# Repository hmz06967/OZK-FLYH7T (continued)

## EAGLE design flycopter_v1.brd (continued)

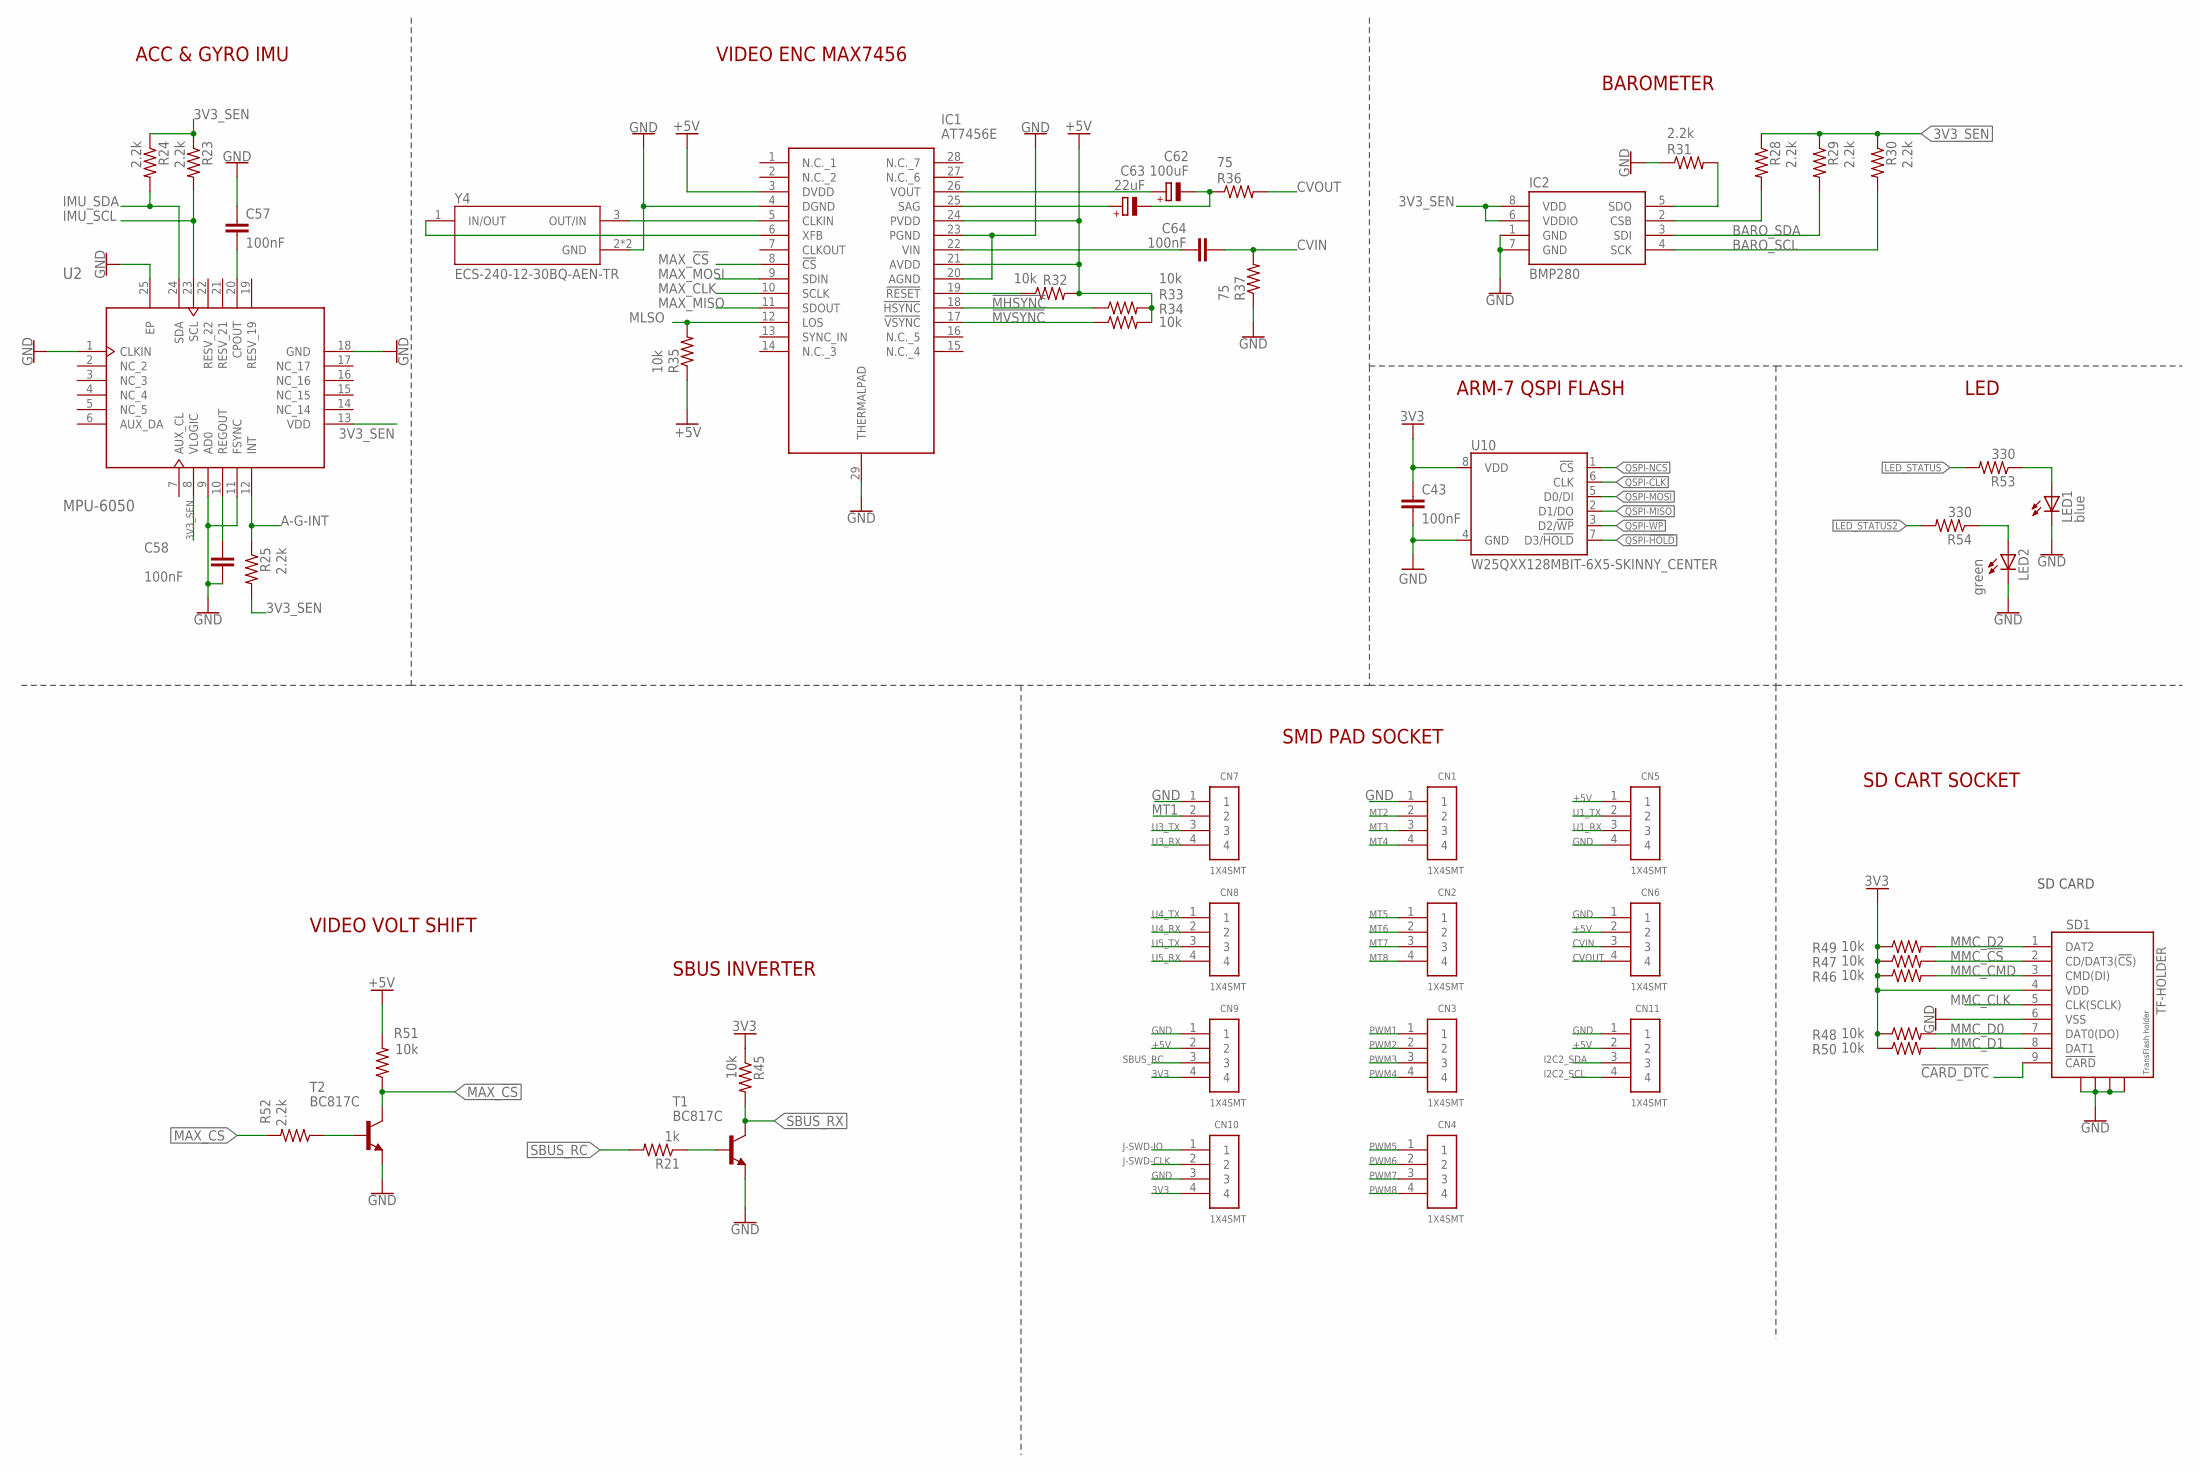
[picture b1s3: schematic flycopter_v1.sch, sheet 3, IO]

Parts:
C43, C57, C58, C64: 100nF; C0603K
C62: 100uF; A/3216-18R
C63: 22uF; A/3216-18R
CN1, CN2, CN3, CN4, CN5, CN6, CN7, CN8, CN9, CN10, CN11: 1X4SMT; 1X4-SMT
IC1: AT7456E; SOP65P640X120-29N
IC2: BMP280
LED1: blue; CHIPLED_0603
LED2: green; CHIPLED_0603
R21: 1k; R0402
R23, R24, R25, R28, R29, R30, R31, R52: 2.2k; R0402
R32, R33, R34, R35, R45, R46, R47, R48, R49, R50, R51: 10k; R0402
R36, R37: 75; R0402
R53, R54: 330; R0402
SD1: TF-HOLDER; TF-PULL
T1, T2: BC817C; SOT23-BEC
U2: MPU-6050; 24-VFQFN
U10: W25QXX128MBIT-6X5-SKINNY_CENTER; WSON-8-6X5-SKINNY_CENTERPAD
Y4: ECS-240-12-30BQ-AEN-TR; XTAL_ECS-240-12-30BQ-AEN-TR

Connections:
3V3: C43.1, CN9.4, CN10.4, R45.1, R46.1, R47.1, R48.1, R49.1, R50.1, SD1.4 (VDD), U10.8 (VDD); also elsewhere on the board
3V3_SEN: IC2.6 (VDDIO), IC2.8 (VDD), R23.1, R24.1, R25.2, R28.1, R29.1, R30.1, U2.8 (VLOGIC), U2.13 (VDD); also elsewhere on the board
!CARD_DTC: SD1.9 (!CARD); also elsewhere on the board
!MHSYNC: IC1.18 (!HSYNC), R33.1
!MVSYNC: IC1.17 (!VSYNC), R34.1
+5V: CN5.1, CN6.2, CN9.2, CN11.2, IC1.3 (DVDD), IC1.21 (AVDD), IC1.24 (PVDD), R32.2, R33.2, R34.2, R35.1, R51.2; also elsewhere on the board
A-G-INT: R25.1, U2.12 (INT)
BARO_SCL: IC2.4 (SCK), R30.2; also elsewhere on the board
BARO_SDA: IC2.3 (SDI), R29.2; also elsewhere on the board
CVIN: C64.2, CN6.3, R37.2
CVOUT: CN6.4, R36.2
GND: C43.2, C57.1, C58.2, CN1.1, CN5.4, CN6.1, CN7.1, CN9.1, CN10.3, CN11.1, IC1.4 (DGND), IC1.20 (AGND), IC1.23 (PGND), IC1.29 (THERMALPAD), IC2.1 (GND), IC2.7 (GND), LED1.C, LED2.C, R31.1, R37.1, SD1.6 (VSS), SD1.S1, SD1.S2, SD1.S3, SD1.S4, T1.E, T2.E, U2.1 (CLKIN), U2.9 (AD0), U2.11 (FSYNC), U2.18 (GND), U2.25 (EP), U10.4 (GND), Y4.2 (GND), Y4.4 (GND); also elsewhere on the board
I2C2_SCL: CN11.4; also elsewhere on the board
I2C2_SDA: CN11.3; also elsewhere on the board
IMU_SCL: R23.2, U2.23 (SCL); also elsewhere on the board
IMU_SDA: R24.2, U2.24 (SDA); also elsewhere on the board
J-SWD-CLK: CN10.2; also elsewhere on the board
J-SWD-IO: CN10.1; also elsewhere on the board
LED_STATUS: R53.2; also elsewhere on the board
LED_STATUS2: R54.2; also elsewhere on the board
MAX_!CS: IC1.8 (!CS), R51.1, T2.C
MAX_CLK: IC1.10 (SCLK); also elsewhere on the board
MAX_CS: R52.2; also elsewhere on the board
MAX_MISO: IC1.11 (SDOUT); also elsewhere on the board
MAX_MOSI: IC1.9 (SDIN); also elsewhere on the board
MLSO: IC1.12 (LOS), R35.2
MMC_!CS: R47.2, SD1.2 (CD/DAT3(!CS!)); also elsewhere on the board
MMC_CLK: SD1.5 (CLK(SCLK)); also elsewhere on the board
MMC_CMD: R46.2, SD1.3 (CMD(DI)); also elsewhere on the board
MMC_D0: R48.2, SD1.7 (DAT0(DO)); also elsewhere on the board
MMC_D1: R50.2, SD1.8 (DAT1); also elsewhere on the board
MMC_D2: R49.2, SD1.1 (DAT2); also elsewhere on the board
MT1: CN7.2; also elsewhere on the board
MT2: CN1.2; also elsewhere on the board
MT3: CN1.3; also elsewhere on the board
MT4: CN1.4; also elsewhere on the board
MT5: CN2.1; also elsewhere on the board
MT6: CN2.2; also elsewhere on the board
MT7: CN2.3; also elsewhere on the board
MT8: CN2.4; also elsewhere on the board
unnamed: R21.1, T1.B
unnamed: LED1.A, R53.1
unnamed: LED2.A, R54.1
unnamed: R52.1, T2.B
unnamed: IC1.19 (!RESET), R32.1
unnamed: C57.2, U2.20 (CPOUT)
unnamed: C58.1, U2.10 (REGOUT)
unnamed: C62.+, IC1.26 (VOUT)
unnamed: IC2.2 (CSB), R28.2
unnamed: IC2.5 (SDO), R31.2
unnamed: C63.+, IC1.25 (SAG)
unnamed: C62.-, C63.-, R36.1
unnamed: C64.1, IC1.22 (VIN)
unnamed: IC1.6 (XFB), Y4.1 (IN/OUT)
unnamed: IC1.5 (CLKIN), Y4.3 (OUT/IN)
PWM1: CN3.1; also elsewhere on the board
PWM2: CN3.2; also elsewhere on the board
PWM3: CN3.3; also elsewhere on the board
PWM4: CN3.4; also elsewhere on the board
PWM5: CN4.1; also elsewhere on the board
PWM6: CN4.2; also elsewhere on the board
PWM7: CN4.3; also elsewhere on the board
PWM8: CN4.4; also elsewhere on the board
QSPI-!HOLD: U10.7 (D3/!HOLD!); also elsewhere on the board
QSPI-!WP: U10.3 (D2/!WP!); also elsewhere on the board
QSPI-CLK: U10.6 (CLK); also elsewhere on the board
QSPI-MISO: U10.2 (D1/DO); also elsewhere on the board
QSPI-MOSI: U10.5 (D0/DI); also elsewhere on the board
QSPI-NCS: U10.1 (!CS!); also elsewhere on the board
SBUS_RC: CN9.3, R21.2
SBUS_RX: R45.2, T1.C; also elsewhere on the board
U1_RX: CN5.3; also elsewhere on the board
U1_TX: CN5.2; also elsewhere on the board
U3_RX: CN7.4; also elsewhere on the board
U3_TX: CN7.3; also elsewhere on the board
U4_RX: CN8.2; also elsewhere on the board
U4_TX: CN8.1; also elsewhere on the board
U5_RX: CN8.4; also elsewhere on the board
U5_TX: CN8.3; also elsewhere on the board

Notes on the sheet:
ACC & GYRO IMU
VIDEO ENC MAX7456
BAROMETER
SD CARD
SBUS INVERTER
SD CART SOCKET
ARM-7 QSPI FLASH
LED
VIDEO VOLT SHIFT
SMD PAD SOCKET

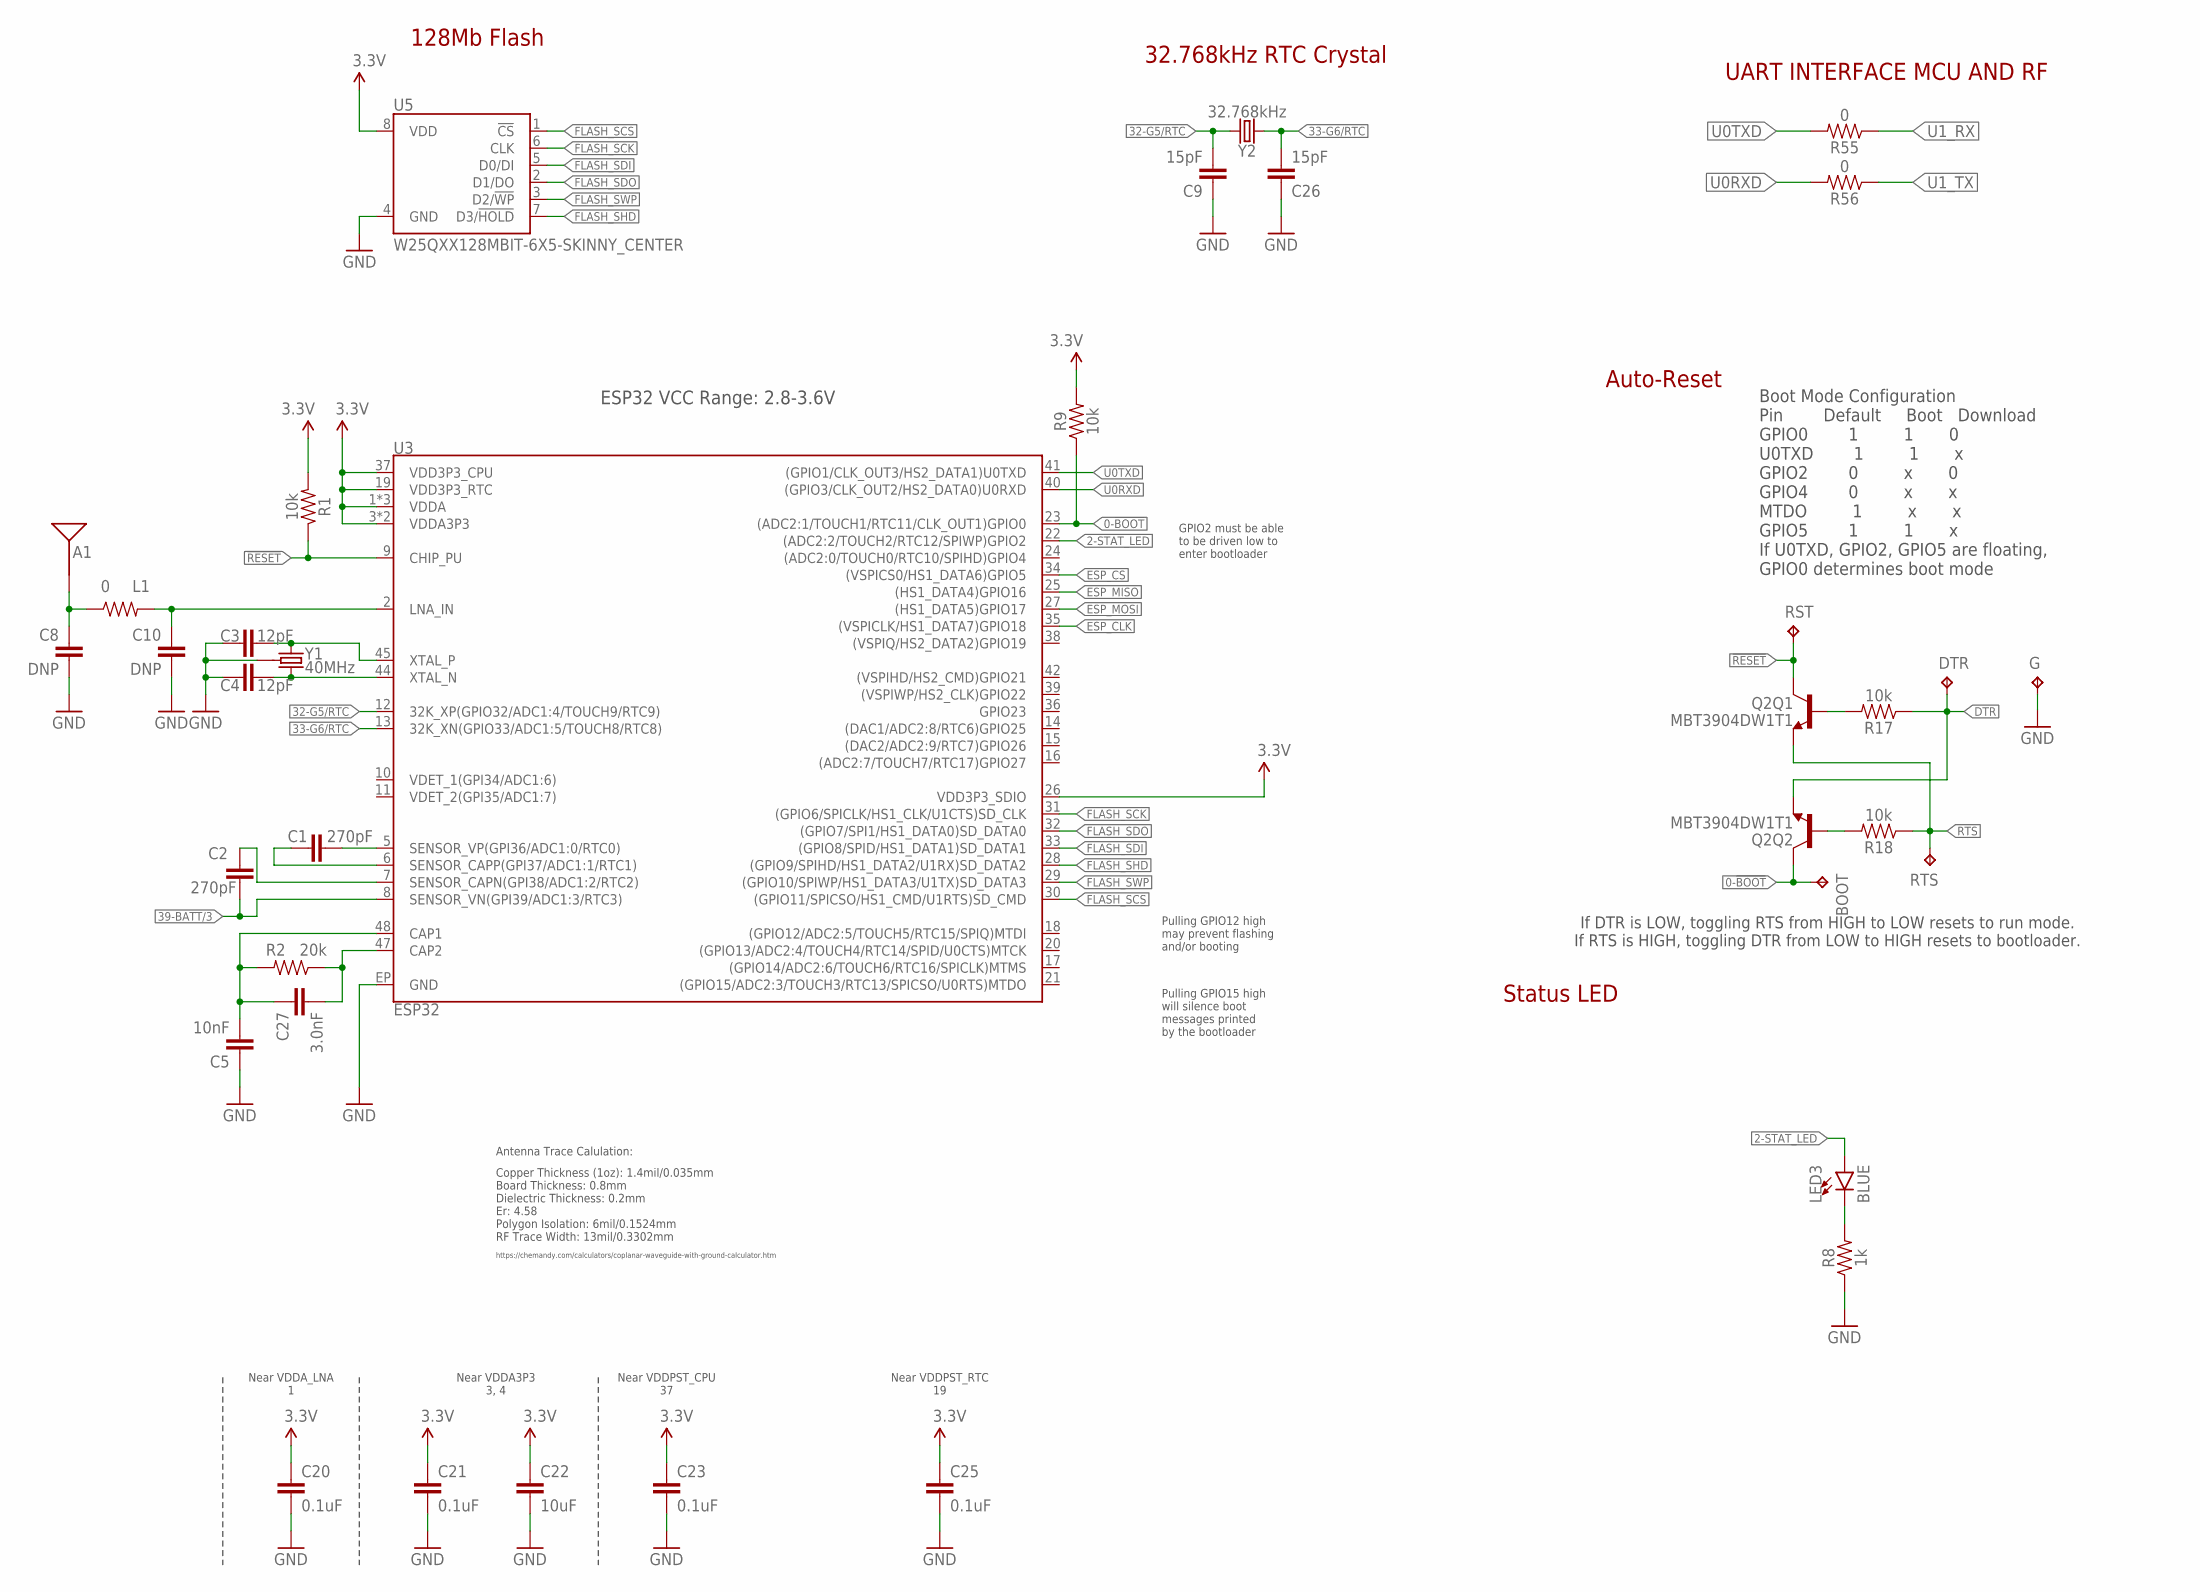
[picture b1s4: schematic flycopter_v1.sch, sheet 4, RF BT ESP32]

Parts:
A1: ANTENNA2.4GHZ-8.0X1.0MM; ANT-2.4GHZ-8.0X1.0MM
BOOT: TPTP06R; TP06R
C1, C2: 270pF; 0402-TIGHT
C3, C4: 12pF; 0402-TIGHT
C5: 10nF; 0402-TIGHT
C8, C10: DNP; 0402-TIGHT
C9, C26: 15pF; 0402-TIGHT
C20, C21, C23, C25: 0.1uF; 0402-TIGHT
C22: 10uF; 0402-TIGHT
C27: 3.0nF; 0402-TIGHT
DTR: TPTP06R; TP06R
G: TPTP06R; TP06R
L1: 0; 0402-TIGHT
LED3: BLUE; LED-0603
Q2: MBT3904DW1T1; SC70-6
R1, R9, R17, R18: 10k; 0402-TIGHT
R2: 20k; 0402-TIGHT
R8: 1k; 0402-TIGHT
R55, R56: 0; 0402-TIGHT
RST: TPTP06R; TP06R
RTS: TPTP06R; TP06R
U3: ESP32; QFN48-0.4MM
U5: W25QXX128MBIT-6X5-SKINNY_CENTER; WSON-8-6X5-SKINNY_CENTERPAD
Y1: 40MHz; CRYSTAL-SMD-2X2.5MM
Y2: 32.768kHz; CRYSTAL-SMD-3.2X1.5MM

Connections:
0-!BOOT!: BOOT.TP, Q2.6 (C), R9.1, U3.23 ((ADC2:1/TOUCH1/RTC11/CLK_OUT1)GPIO0)
2-STAT_LED: LED3.A, U3.22 ((ADC2:2/TOUCH2/RTC12/SPIWP)GPIO2)
3.3V: C20.1, C21.1, C22.1, C23.1, C25.1, R1.2, R9.2, U3.1 (VDDA), U3.3 (VDDA3P3), U3.4 (VDDA3P3), U3.19 (VDD3P3_RTC), U3.26 (VDD3P3_SDIO), U3.37 (VDD3P3_CPU), U3.43 (VDDA), U3.46 (VDDA), U5.8 (VDD); also elsewhere on the board
32-G5/RTC: C9.2, U3.12 (32K_XP(GPIO32/ADC1:4/TOUCH9/RTC9)), Y2.P$1 (1)
33-G6/RTC: C26.2, U3.13 (32K_XN(GPIO33/ADC1:5/TOUCH8/RTC8)), Y2.P$2 (2)
36: C1.2, U3.5 (SENSOR_VP(GPI36/ADC1:0/RTC0))
37: C1.1, U3.6 (SENSOR_CAPP(GPI37/ADC1:1/RTC1))
38: C2.1, U3.7 (SENSOR_CAPN(GPI38/ADC1:2/RTC2))
39-BATT/3: C2.2, U3.8 (SENSOR_VN(GPI39/ADC1:3/RTC3))
!RESET: Q2.3 (C), R1.1, RST.TP, U3.9 (CHIP_PU)
CAP_10N: C5.2, C27.1, R2.2, U3.48 (CAP1)
DTR: DTR.TP, Q2.1 (E), R17.1
ESP_CLK: U3.35 ((VSPICLK/HS1_DATA7)GPIO18); also elsewhere on the board
ESP_CS: U3.34 ((VSPICS0/HS1_DATA6)GPIO5); also elsewhere on the board
ESP_MISO: U3.25 ((HS1_DATA4)GPIO16); also elsewhere on the board
ESP_MOSI: U3.27 ((HS1_DATA5)GPIO17); also elsewhere on the board
FLASH_SCK: U3.31 ((GPIO6/SPICLK/HS1_CLK/U1CTS)SD_CLK), U5.6 (CLK)
FLASH_SCS: U3.30 ((GPIO11/SPICSO/HS1_CMD/U1RTS)SD_CMD), U5.1 (!CS!)
FLASH_SDI: U3.33 ((GPIO8/SPID/HS1_DATA1)SD_DATA1), U5.5 (D0/DI)
FLASH_SDO: U3.32 ((GPIO7/SPI1/HS1_DATA0)SD_DATA0), U5.2 (D1/DO)
FLASH_SHD: U3.28 ((GPIO9/SPIHD/HS1_DATA2/U1RX)SD_DATA2), U5.7 (D3/!HOLD!)
FLASH_SWP: U3.29 ((GPIO10/SPIWP/HS1_DATA3/U1TX)SD_DATA3), U5.3 (D2/!WP!)
GND: C3.1, C4.1, C5.1, C8.2, C9.1, C10.2, C20.2, C21.2, C22.2, C23.2, C25.2, C26.1, G.TP, R8.1, U3.EP (GND), U5.4 (GND), Y1.P2 (GND), Y1.P4 (GND); also elsewhere on the board
unnamed: Q2.5 (B), R17.2
unnamed: Q2.2 (B), R18.2
unnamed: C3.2, U3.45 (XTAL_P), Y1.P1 (1)
unnamed: C4.2, U3.44 (XTAL_N), Y1.P3 (2)
unnamed: LED3.C, R8.2
unnamed: C27.2, R2.1, U3.47 (CAP2)
unnamed: A1.FEED, C8.1, L1.1
unnamed: C10.1, L1.2, U3.2 (LNA_IN)
RTS: Q2.4 (E), R18.1, RTS.TP
U0RXD: R56.2, U3.40 ((GPIO3/CLK_OUT2/HS2_DATA0)U0RXD)
U0TXD: R55.2, U3.41 ((GPIO1/CLK_OUT3/HS2_DATA1)U0TXD)
U1_RX: R55.1; also elsewhere on the board
U1_TX: R56.1; also elsewhere on the board

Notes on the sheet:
Boot Mode Configuration Pin Default Boot Download GPIO0 1 1 0 U0TXD 1 1 x GPIO2 0 x 0 GPIO4 0 x x MTDO 1 x x GPIO5 1 1 x If U0TXD, GPIO2, GPIO5 are floating, GPIO0 determines boot mode
Auto-Reset
Near VDDA_LNA 1
Near VDDA3P3 3, 4
Near VDDPST_CPU 37
Near VDDPST_RTC 19
128Mb Flash
32.768kHz RTC Crystal
ESP32 VCC Range: 2.8-3.6V
Antenna Trace Calulation:
Copper Thickness (1oz): 1.4mil/0.035mm Board Thickness: 0.8mm Dielectric Thickness: 0.2mm Er: 4.58 Polygon Isolation: 6mil/0.1524mm RF Trace Width: 13mil/0.3302mm
https://chemandy.com/calculators/coplanar-waveguide-with-ground-calculator.htm
GPIO2 must be able to be driven low to enter bootloader
Pulling GPIO12 high may prevent flashing and/or booting
Pulling GPIO15 high will silence boot messages printed by the bootloader
UART INTERFACE MCU AND RF
Status LED
If DTR is LOW, toggling RTS from HIGH to LOW resets to run mode. If RTS is HIGH, toggling DTR from LOW to HIGH resets to bootloader.

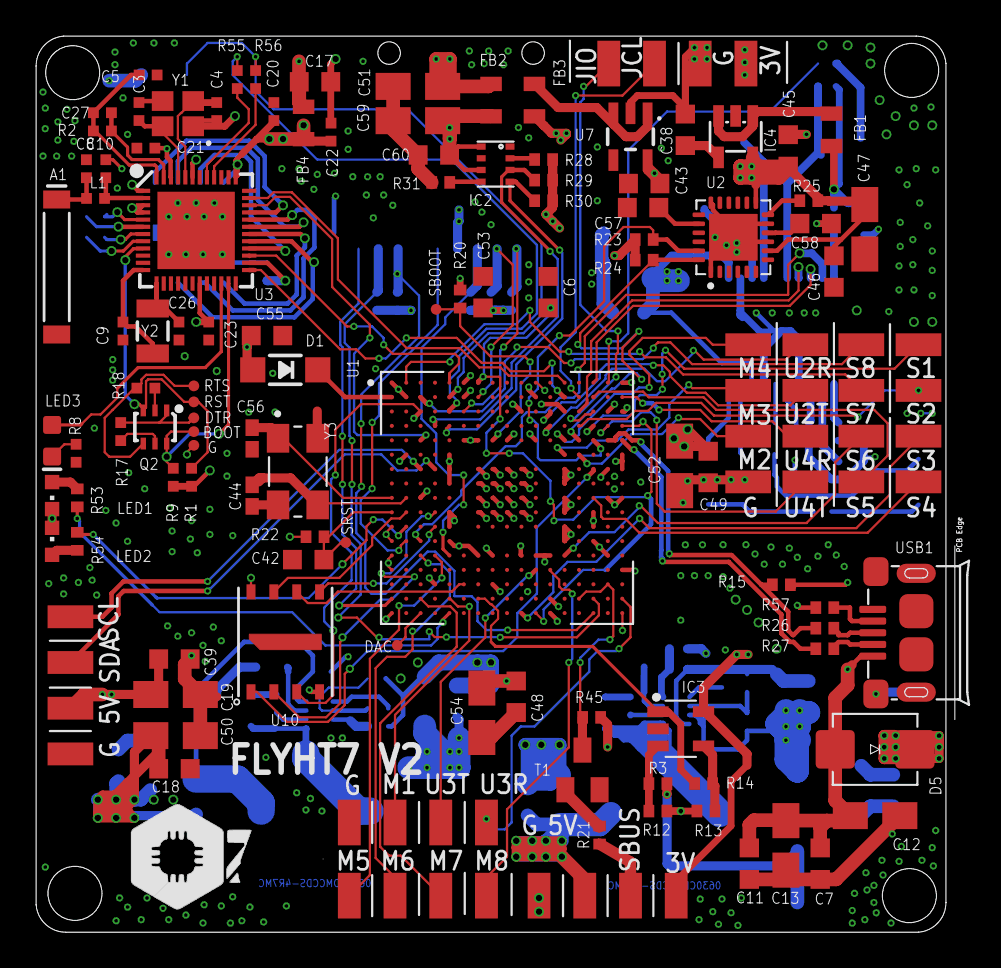
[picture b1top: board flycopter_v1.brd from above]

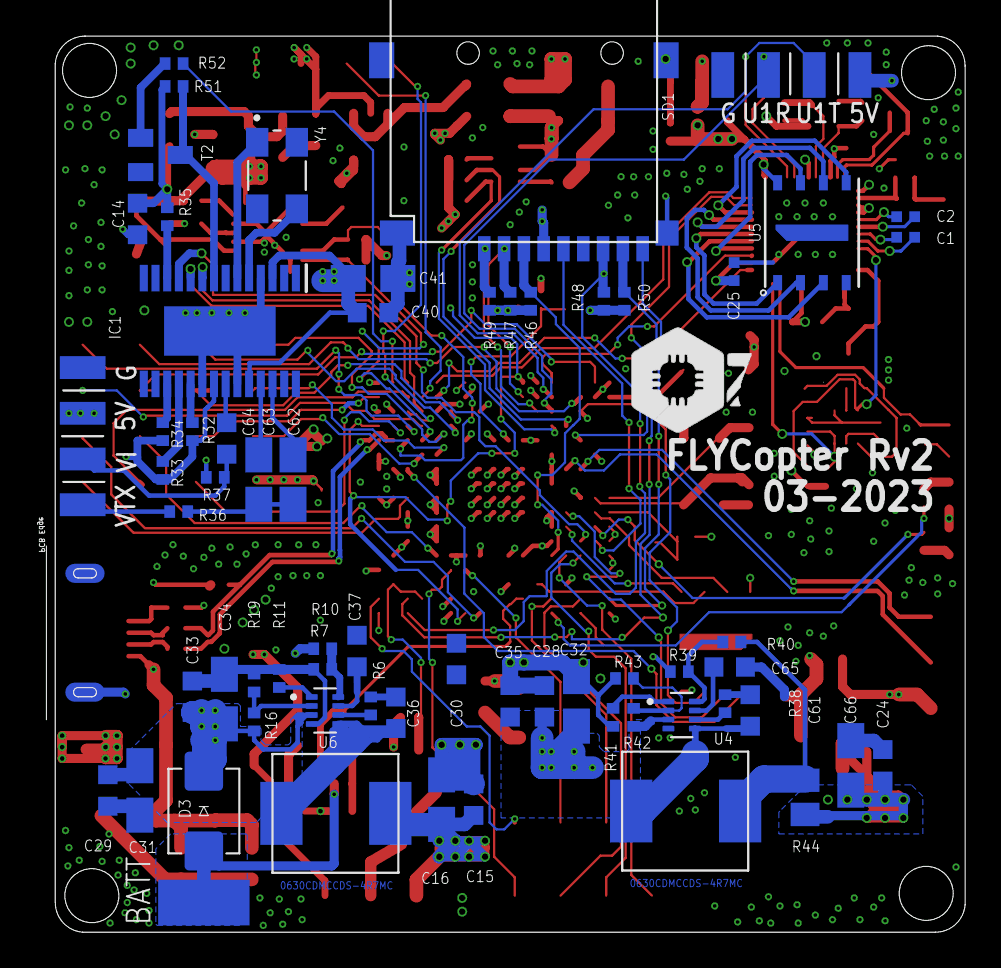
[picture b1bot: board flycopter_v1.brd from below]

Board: 4 copper layers, 51.6 x 49.7 mm, 178 parts (65 on the bottom side), 148 nets.

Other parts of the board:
U$1, U$2: OZK_20

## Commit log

2023-03-30 add image
2023-03-30 fixed image
